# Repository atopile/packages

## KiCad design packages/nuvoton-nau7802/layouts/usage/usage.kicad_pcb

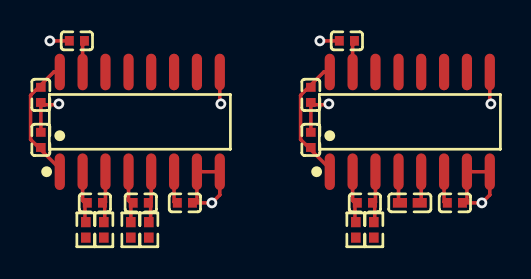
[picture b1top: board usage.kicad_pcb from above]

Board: 2 copper layers, 20 parts (0 on the bottom side), 14 nets.

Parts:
C1, C2, C3, C4, C5, C6, C8: 1F; C0402
C7: 4.7e-F; C0402
C9, C10, C11, C12: 1e-06F; C0402
R1, R2, R3, R4, R5, R6: 49.9Ω; R0402
U1, U2: SOP-16_L9.9-W3.9-P1.27-LS6.0-BL

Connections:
dvdd_cap-power-hv: C10.1, C12.1, U1.15, U2.15
filter_cap-power-lv-1_N: C5.2, R6.2, U2.2
filter_cap-power-lv_N: C2.2, R4.2, U1.4
filter_cap-power-output-1_P: C5.1, R5.2, U2.3
filter_cap-power-output_P: C2.1, R3.2, U1.5
hv: C3.1, C9.1, U1.1, U1.16
input_termination_cap-power-hv: C7.1, U2.4
input_termination_cap-power-lv: C7.2, U2.5
lv: C3.2, C4.2, C6.2, C8.2, C9.2, C10.2, C11.2, C12.2, U1.7, U1.8, U1.9, U2.7, U2.8, U2.9
lv_N: C1.2, R2.2, U1.2
output_P: C1.1, R1.2, U1.3
refp_cap-power-hv: C6.1, C11.1, U2.1, U2.16
vbg_cap-power-hv: C4.1, U1.6
vbg_cap-power-hv-1: C8.1, U2.6

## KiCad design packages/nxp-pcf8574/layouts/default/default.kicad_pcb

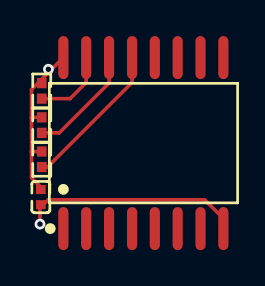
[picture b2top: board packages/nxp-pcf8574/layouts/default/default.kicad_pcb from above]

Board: 2 copper layers, 5 parts (0 on the bottom side), 5 nets.

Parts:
C1: 100nF; C0402
R1, R2, R3: 10kΩ; R0402
U1: SOIC-16_L10.3-W7.5-P1.27-LS10.3-BL

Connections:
SCL: R2.1, U1.14
SDA: R3.1, U1.15
hv: C1.1, R1.2, R2.2, R3.2, U1.16
lv: C1.2, U1.1, U1.2, U1.3, U1.8
nINT: R1.1, U1.13

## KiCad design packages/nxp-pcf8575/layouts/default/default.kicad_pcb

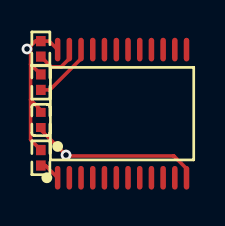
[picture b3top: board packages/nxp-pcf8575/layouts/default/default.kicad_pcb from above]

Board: 2 copper layers, 5 parts (0 on the bottom side), 5 nets.

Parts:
C1: 1±10.0%F; C0402
R1, R2, R3: 10000±1.0%Ω; R0402
U1: SSOP-24_L8.1-W5.3-P0.65-LS7.8-BL

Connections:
SCL: R1.1, U1.22
SDA: R2.1, U1.23
hv: C1.1, R1.2, R2.2, R3.2, U1.24
lv: C1.2, U1.2, U1.3, U1.12, U1.21
nINT: R3.1, U1.1

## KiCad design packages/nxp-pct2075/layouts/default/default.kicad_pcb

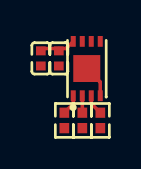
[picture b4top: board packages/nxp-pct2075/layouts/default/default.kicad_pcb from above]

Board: 2 copper layers, 6 parts (0 on the bottom side), 5 nets.

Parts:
C1, C2: 100nF; C0402
R1, R2, R3: 10kΩ; R0402
U1: HWSON-8_L2.0-W3.0-P0.50-BL-EP1.5

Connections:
OS: R3.2, U1.3
SCL: R1.1, U1.2
SDA: R2.1, U1.1
hv: C1.1, C2.1, R1.2, R2.2, R3.1, U1.8
lv: C1.2, C2.2, U1.4, U1.5, U1.6, U1.7, U1.9

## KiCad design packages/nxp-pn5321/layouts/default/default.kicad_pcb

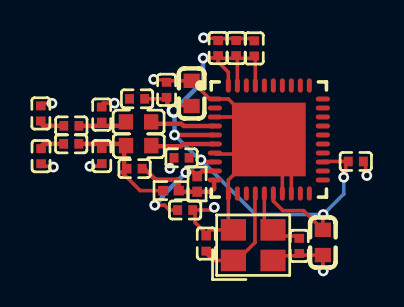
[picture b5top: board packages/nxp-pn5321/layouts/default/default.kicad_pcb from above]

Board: 2 copper layers, 25 parts (0 on the bottom side), 12 nets.

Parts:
C1, C2, C3, C4, C6, C8, C9, C10, C11, C12, C13, C14, C15, C16, C17, C18, C19: 0F; C0402
C5, C7: 0F; C0603
L1, L2: IND-SMD_L1.6-W0.8-1
R4, R5: 1000Ω; R0402
U1: QFN-40_L6.0-W6.0-P0.50-BL-EP4.1
X1: CRYSTAL-SMD_4P-L3.2-W2.5-BL

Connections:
4: L1.2, U1.4
6: L2.2, U1.6
antenna_output_N: C15.1, C16.2
antenna_output_P: C13.1, C14.2
hv: C1.1, C2.1, C5.1, C6.1, C7.1, C8.1, C9.1, C10.1, C11.1, U1.5, U1.8, U1.16, U1.23, U1.37, U1.39, U1.40
load_caps[0]-power-hv: C3.1, U1.14, X1.1
load_caps[1]-power-hv: C4.1, U1.15, X1.3
lv: C1.2, C2.2, C3.2, C4.2, C5.2, C6.2, C7.2, C8.2, C9.2, C10.2, C11.2, C13.2, C15.2, C17.2, C18.2, C19.2, U1.1, U1.3, U1.7, U1.11, U1.17, U1.18, U1.41, X1.2, X1.4
rx_capacitor-power-lv: C12.2, R4.2, R5.2, U1.10
tx_1_mid: C14.1, C17.1, L1.1
tx_2_mid: C12.1, C16.1, C18.1, L2.1, R4.1
vmid_cap-power-hv: C19.1, R5.1, U1.9
